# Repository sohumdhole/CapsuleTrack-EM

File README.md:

# CapsuleTrack-EM

**A patient-worn low-frequency magnetic tracking simulator for wireless capsule endoscopy.**

A wearable abdominal patch of planar coils transmits 14–31.5 kHz magnetic fields. A
3-axis coil inside the capsule senses them, and a 6-DOF solver recovers the capsule's
position and orientation. The project covers the whole chain:

1. tissue electromagnetics;
2. coil and driver design (SPICE);
3. KiCad hardware files;
4. a pose solver;
5. a Monte Carlo accuracy study across **real human body sizes (ANSUR II)**.

> **Simulation and design study only.** Nothing was fabricated or measured on hardware,
> phantoms or people.

## Key results

Nominal design: 8 coils, 80 mA, 0.5 mm / 1° patch-placement uncertainty, 1 nT ambient
interference.

| | |
|---|---|
| Tissue at 1–50 kHz | Skin depth ≥ 3.1 m, so the abdomen is quasi-static. Worst-case eddy bias ≤ 0.18 mm at 31.5 kHz (20 cm path) |
| Patch coil | 203 µH, 13.3 Ω, 65 turns over 4 layers, 0.057 A·m²/A, all derived from geometry |
| Driver (ngspice) | 80.0 mA fundamental from a 3.3 V phase-shifted bridge. A ±5 % component tolerance cuts the current by up to 16 %, so closed-loop control is needed |
| Exposure | Induced E-field 12.8–24× below the ICNIRP 2010 basic restriction |
| Accuracy, 4,800 poses / 600 subjects | **Median 1.18 mm**, 95th percentile 4.2 mm, 41 % ≤ 1 mm, orientation median 1.37° |
| Body-size effect | Median 1.00 mm in the slimmest waist-depth quartile, 1.44 mm in the largest |
| Dominant error source | Patch geometry knowledge: median 0.28 mm with exact geometry vs 1.16 mm at 0.5 mm / 1° |
| Per-patient anatomy | A fixed nominal body doubles the error (2.46 vs 1.16 mm) |
| Field model | The point dipole is inadequate near the patch (2.03 vs 1.16 mm) |
| KiCad patch | **DRC: 0 violations, 0 unconnected** (KiCad 7.0.11) |

Full write-up: [`report/CapsuleTrack-EM_Technical_Report.md`](report/CapsuleTrack-EM_Technical_Report.md)

## Data (real, public)

| Dataset | Use |
|---|---|
| Gabriel, Lau & Gabriel (1996) 4-Cole–Cole tissue parameters, *Phys. Med. Biol.* 41:2271 | Conductivity, permittivity, skin depth |
| ANSUR II public release, 4,082 men and 1,986 women | Per-subject abdomen geometry and patch shape |
| ICNIRP 2010 (1 Hz–100 kHz) | Exposure limits |

Provenance, hashes and caveats: `data/raw/*/SOURCE.md`.

## Repository layout

```
capsuletrack/      library
  tissue.py          Cole-Cole model, conductivity, skin depth, induction number
  coils.py           planar spiral geometry -> L (Maxwell mutual sums), R, moment
  field.py           exact circular-loop field (elliptic integrals), dipole field
  anatomy.py         ANSUR II loader, elliptic abdomen, conformal patch, workspace
  system.py          FDM transmitter patch, capsule receiver noise, error model
  solver.py          rotation-invariant seeding + Procrustes + Levenberg-Marquardt, CRLB
  montecarlo.py      parallel Monte Carlo + summaries
scripts/           01_tissue ... 06_kicad, run_all.py
hardware/
  ltspice/           coil_driver_14kHz / 31.5kHz  (.cir netlists + .asc schematics)
  kicad/patch/       4-layer flex transmitter patch (.kicad_pcb, footprint lib)
  kicad/driver/      driver schematic (.kicad_sch + PDF)
  kicad/bom.csv
results/tables/    every number in the report, as CSV
results/figures/   every figure in the report
report/            technical report
tests/             unit tests (field vs analytic, dipole limit, tissue, solver)
```

## Reproduce

```bash
pip install -r requirements.txt
python -m pytest -q tests            # 8 tests
python scripts/run_all.py            # all tables, figures, SPICE runs and KiCad files
```

Notes:

- `03_driver_spice.py` needs `ngspice` on the PATH.
- The KiCad files open in KiCad 7 or later. DRC was run with KiCad 7's `pcbnew` Python
  API.
- The full Monte Carlo study (script 04) takes about 10 min on 2 cores.

## Limitations

- The abdomen is an elliptic cylinder from ANSUR measurements. There is no organ
  segmentation and no respiration.
- The abdominal wall thickness is fixed.
- The ANSUR sample is military, not a patient population.
- Receiver and ambient noise levels are assumptions, varied in the sweeps.
- Metallic distortion is out of scope.
- The exposure check is a first-order estimate, not voxel dosimetry.
- Driver-schematic IC pinouts must be verified against datasheets before layout.

## Licence

Code: MIT. ANSUR II is a U.S. Government public-domain work. The tissue parameters are
cited scientific data.

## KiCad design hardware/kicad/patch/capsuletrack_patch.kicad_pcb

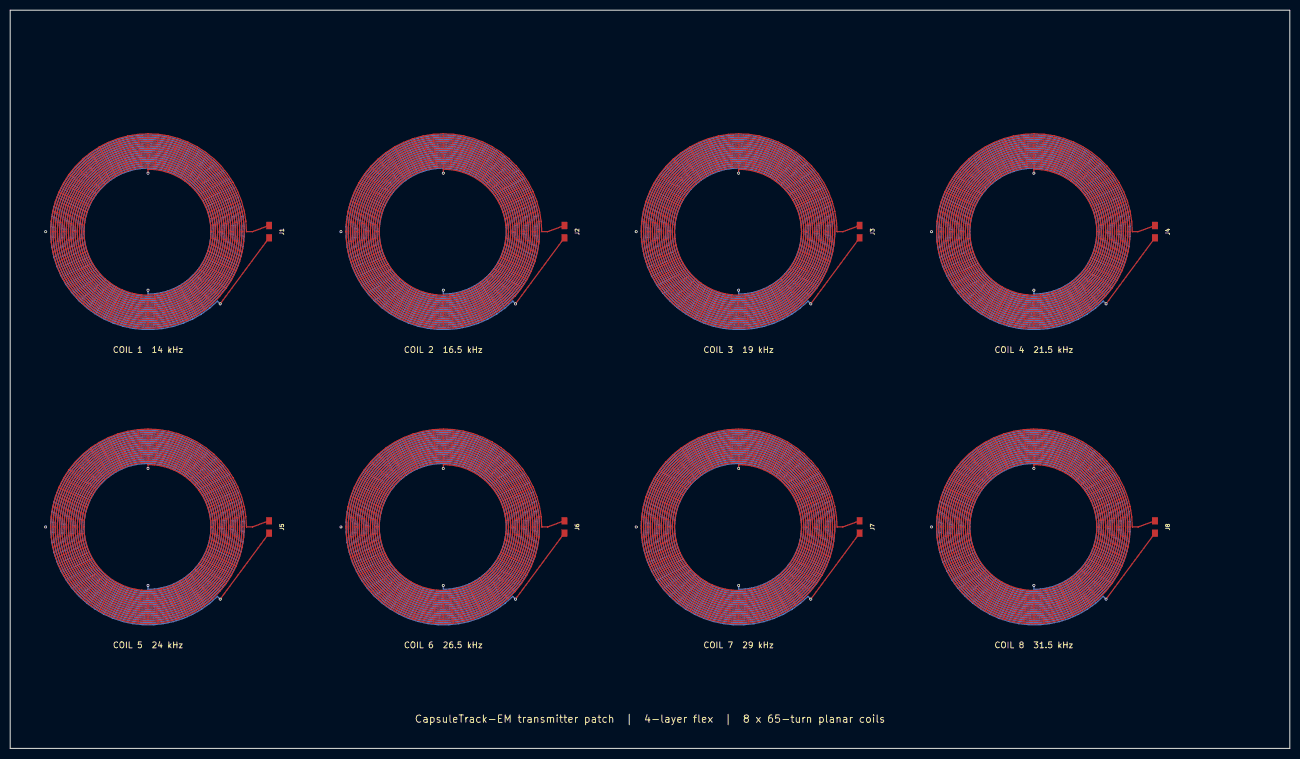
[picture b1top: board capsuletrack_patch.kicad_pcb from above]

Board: 4 copper layers, 260.0 x 150.0 mm, 8 parts (0 on the bottom side), 8 nets.

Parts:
J1: COIL1_LEADS; CoilLead_2Pad
J2: COIL2_LEADS; CoilLead_2Pad
J3: COIL3_LEADS; CoilLead_2Pad
J4: COIL4_LEADS; CoilLead_2Pad
J5: COIL5_LEADS; CoilLead_2Pad
J6: COIL6_LEADS; CoilLead_2Pad
J7: COIL7_LEADS; CoilLead_2Pad
J8: COIL8_LEADS; CoilLead_2Pad

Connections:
COIL1: J1.1, J1.2
COIL2: J2.1, J2.2
COIL3: J3.1, J3.2
COIL4: J4.1, J4.2
COIL5: J5.1, J5.2
COIL6: J6.1, J6.2
COIL7: J7.1, J7.2
COIL8: J8.1, J8.2
